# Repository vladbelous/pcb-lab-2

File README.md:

## PCB Lab #2 - Current Sensing

"Lab"-style PCB for experimenting with different current sensing circuits.

TODO: add more description

## Schematic:

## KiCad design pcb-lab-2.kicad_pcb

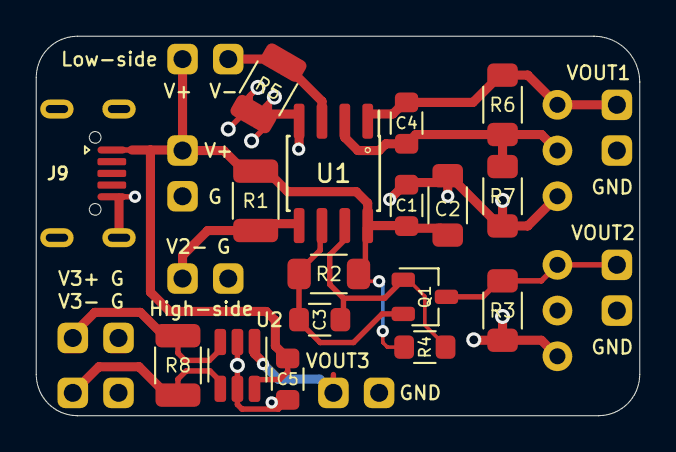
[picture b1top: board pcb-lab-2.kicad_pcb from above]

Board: 2 copper layers, 33.5 x 21.1 mm, 27 parts (0 on the bottom side), 12 nets.

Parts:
C1, C3, C4, C5: 0.1u; 0805_HS
C2: 1u; 1206_HS
J1, J2, J3, J4, J5, J6, J7, J8: Conn_01x02; Pin_Header_Straight_1x02_Pitch2.54mm
J9: USB_B_Micro; USB-micro-B_4-legs_Banggood
Q1: FDV302P; SOT-23_HS
R1, R5, R8: 1; 1210_HS
R2, R7: 100; 1206_HS
R3: 10k; 1206_HS
R4: 100k; 0805_HS
R6: 9.9k; 1206_HS
RV1, RV2: R_POT; Conn_01x03_small
U1: NCS2333; SOIC-8_3.9x4.9mm_Pitch1.27mm_HS
U2: INA181; SOT-23-6_HS

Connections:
GND: C1.2, C2.2, C5.2, J1.2, J2.2, J3.2, J5.2, J6.2, J7.2, J8.2, J9.5, J9.6, R3.2, R5.1, R7.2, RV1.2, RV1.3, RV2.3, U1.4, U2.2, U2.5
unnamed: C3.1, Q1.1, R4.1, U1.7
unnamed: C3.2, Q1.2, R2.2, U1.6
unnamed: C4.2, R6.2, R7.1, RV2.2, U1.2
V1-: J4.2, R5.2, U1.3
V2-: J2.1, R1.1, U1.5
V3+: J6.1, R8.2, U2.3
V3-: J7.1, R8.1, U2.4
V+: C1.1, C2.1, C5.1, J1.1, J4.1, J9.1, R1.2, R2.1, R4.2, U1.8, U2.6
VOUT1: C4.1, J5.1, R6.1, RV2.1, U1.1
VOUT2: J3.1, Q1.3, R3.1, RV1.1
VOUT3: J8.1, U2.1

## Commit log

2020-06-15 Two different 2-stage op-amp configs
2020-06-22 Add simple current sensing: low side and high side
2020-06-23 Add INA181 high-side sensing
2020-06-24 Simplify to just sensing: op-amp low-side and high-side; INA181 high-side
2020-06-26 Finished and annotated schematic
2020-06-26 Fix GND annotation
2020-06-26 Footprint assignment
2020-06-26 Bug fixes
2020-06-26 Create netlist
2020-06-27 Initial PCB layout
2020-06-27 Make board smaller
2020-06-28 Complete routing
2020-06-28 Add silkscreen
2020-06-28 Schematic PDF
2020-06-29 Add README and png schematic
2020-06-29 Add license

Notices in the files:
pcb-lab-2.kicad_pcb:
CC BY-SA 4.0
